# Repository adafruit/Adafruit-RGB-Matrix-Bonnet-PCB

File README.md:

## Adafruit RGB LED Matrix Display Bonnet PCB

<a href="http://www.adafruit.com/products/3211"><br/>
Click here to purchase one from the Adafruit shop</a>

PCB files for the Adafruit RGB Matrix Bonnet. Format is EagleCAD schematic and board layout

For more details, check out the product page at
* https://www.adafruit.com/product/3211

### Description

You can now create a dazzling display with your Raspberry Pi with the Adafruit RGB Matrix Bonnet. These boards plug into your Pi and makes it super easy to control RGB matrices such as those we stock in the shop and create a colorful scrolling display or mini LED wall with ease.

"Bonnet" boards work on any Raspberry Pi with a 40-pin GPIO header — Zero, Zero W/WH, Model A+, B+, Pi 2 and Pi 3. They do not work with older 26-pin boards like the original Model A or B. Note with the Pi Zero you may need to solder a header on the Pi board; it’s normally unpopulated on that model.

We also have an older, HAT version of our RGB Matrix design. The HAT version does not come fully assembled, does not support 1/32-scan matrices, but does come with a real time clock (RTC)

This bonnet will make your matrix projects super easy and avoids wiring complexity.

Please note: this Bonnet is only for use with HUB75 type RGB matrices. Not for use with NeoPixel, DotStar, or other 'addressable' LEDs.

### License

Adafruit invests time and resources providing this open source design, please support Adafruit and open-source hardware by purchasing products from [Adafruit](https://www.adafruit.com)!

Designed for Adafruit Industries.

Creative Commons Attribution/Share-Alike, all text above must be included in any redistribution. See license.txt for additional details.

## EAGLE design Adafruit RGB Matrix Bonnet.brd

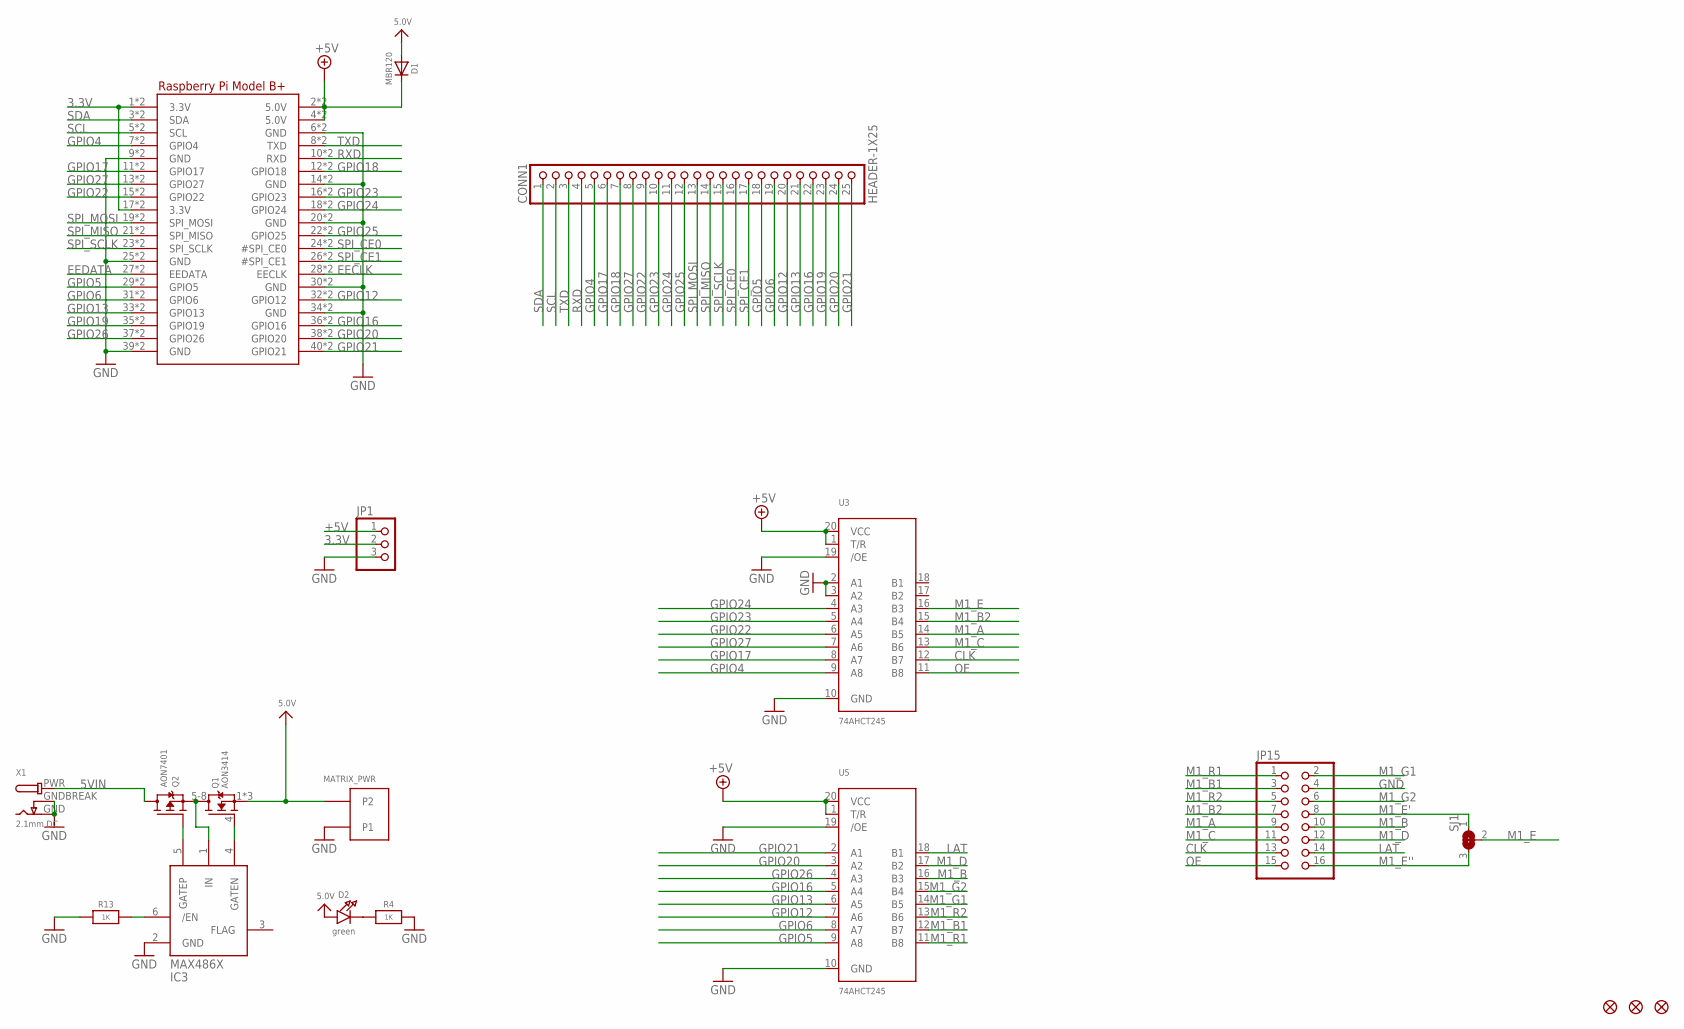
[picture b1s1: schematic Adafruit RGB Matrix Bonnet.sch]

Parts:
CONN1: HEADER-1X25; 1X25_ROUND_70MIL
D1: MBR120; SOD-123
D2: green; CHIPLED_0805_NOOUTLINE
FID1, FID2, FID3: FIDUCIAL_1MM
IC3: MAX4866T; SOT23-6
JP1: HEADER-1X376MIL; 1X03_ROUND_76
JP15: HEADER-2X8_SHROUDED; 2X08_SHROUDED
MATRIX_PWR: PINHEAD; TERMBLOCK508
Q1: AON3414; POWERPAK-1212-8
Q2: AON7401; POWERDI3333
R4, R13: 1K; 0805-NO
RPI1: RASPBERRYPI_BPLUS_BONNET_THMSMT; PI_BONNET_THMSMT
SJ1: SOLDERJUMPER_2WAY; SOLDERJUMPER_2WAY_OPEN_NOPASTE
U3, U5: 74AHCT245; TSSOP20
X1: 2.1mm DC; DCJACK_2MM_PTH

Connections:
3.3V: JP1.2, RPI1.1 (3.3V), RPI1.17 (3.3V), RPI1.S1 (3.3V), RPI1.S17 (3.3V)
5.0V: D1.A, D2.A, MATRIX_PWR.P$4 (P2), Q1.1 (S), Q1.2 (S), Q1.3 (S)
5VIN: Q2.5678 (D), X1.PWR
+5V: D1.C, JP1.1, RPI1.2 (5.0V), RPI1.4 (5.0V), RPI1.S2 (5.0V), RPI1.S4 (5.0V), U3.1 (T/R), U3.20 (VCC), U5.1 (T/R), U5.20 (VCC)
CLK: JP15.13, U3.12 (B7)
EECLK: RPI1.28 (EECLK), RPI1.S28 (EECLK)
EEDATA: RPI1.27 (EEDATA), RPI1.S27 (EEDATA)
GND: IC3.2 (GND), JP1.3, JP15.4, MATRIX_PWR.P$3 (P1), R4.2, R13.1, RPI1.6 (GND), RPI1.9 (GND), RPI1.14 (GND), RPI1.20 (GND), RPI1.25 (GND), RPI1.30 (GND), RPI1.34 (GND), RPI1.39 (GND), RPI1.S6 (GND), RPI1.S9 (GND), RPI1.S14 (GND), RPI1.S20 (GND), RPI1.S25 (GND), RPI1.S30 (GND), RPI1.S34 (GND), RPI1.S39 (GND), U3.2 (A1), U3.3 (A2), U3.10 (GND), U3.19 (/OE), U5.10 (GND), U5.19 (/OE), X1.GND, X1.GNDBREAK
GPIO4: CONN1.5, RPI1.7 (GPIO4), RPI1.S7 (GPIO4), U3.9 (A8)
GPIO5: CONN1.18, RPI1.29 (GPIO5), RPI1.S29 (GPIO5), U5.9 (A8)
GPIO6: CONN1.19, RPI1.31 (GPIO6), RPI1.S31 (GPIO6), U5.8 (A7)
GPIO12: CONN1.20, RPI1.32 (GPIO12), RPI1.S32 (GPIO12), U5.7 (A6)
GPIO13: CONN1.21, RPI1.33 (GPIO13), RPI1.S33 (GPIO13), U5.6 (A5)
GPIO16: CONN1.22, RPI1.36 (GPIO16), RPI1.S36 (GPIO16), U5.5 (A4)
GPIO17: CONN1.6, RPI1.11 (GPIO17), RPI1.S11 (GPIO17), U3.8 (A7)
GPIO18: CONN1.7, RPI1.12 (GPIO18), RPI1.S12 (GPIO18)
GPIO19: CONN1.23, RPI1.35 (GPIO19), RPI1.S35 (GPIO19)
GPIO20: CONN1.24, RPI1.38 (GPIO20), RPI1.S38 (GPIO20), U5.3 (A2)
GPIO21: CONN1.25, RPI1.40 (GPIO21), RPI1.S40 (GPIO21), U5.2 (A1)
GPIO22: CONN1.9, RPI1.15 (GPIO22), RPI1.S15 (GPIO22), U3.6 (A5)
GPIO23: CONN1.10, RPI1.16 (GPIO23), RPI1.S16 (GPIO23), U3.5 (A4)
GPIO24: CONN1.11, RPI1.18 (GPIO24), RPI1.S18 (GPIO24), U3.4 (A3)
GPIO25: CONN1.12, RPI1.22 (GPIO25), RPI1.S22 (GPIO25)
GPIO26: RPI1.37 (GPIO26), RPI1.S37 (GPIO26), U5.4 (A3)
GPIO27: CONN1.8, RPI1.13 (GPIO27), RPI1.S13 (GPIO27), U3.7 (A6)
LAT: JP15.14, U5.18 (B1)
M1_A: JP15.9, U3.14 (B5)
M1_B: JP15.10, U5.16 (B3)
M1_B1: JP15.3, U5.12 (B7)
M1_B2: JP15.7, U3.15 (B4)
M1_C: JP15.11, U3.13 (B6)
M1_D: JP15.12, U5.17 (B2)
M1_E: SJ1.2, U3.16 (B3)
M1_E': JP15.8, SJ1.1
M1_E'': JP15.16, SJ1.3
M1_G1: JP15.2, U5.14 (B5)
M1_G2: JP15.6, U5.15 (B4)
M1_R1: JP15.1, U5.11 (B8)
M1_R2: JP15.5, U5.13 (B6)
unnamed: IC3.6 (/EN), R13.2
unnamed: D2.C, R4.1
unnamed: IC3.1 (IN), Q1.5-8 (D), Q2.1 (S), Q2.2 (S), Q2.3 (S)
unnamed: IC3.4 (GATEN), Q1.4 (G)
unnamed: IC3.5 (GATEP), Q2.4 (G)
OE: JP15.15, U3.11 (B8)
RXD: CONN1.4, RPI1.10 (RXD), RPI1.S10 (RXD)
SCL: CONN1.2, RPI1.5 (SCL), RPI1.S5 (SCL)
SDA: CONN1.1, RPI1.3 (SDA), RPI1.S3 (SDA)
SPI_CE0: CONN1.16, RPI1.24 (#SPI_CE0), RPI1.S24 (#SPI_CE0)
SPI_CE1: CONN1.17, RPI1.26 (#SPI_CE1), RPI1.S26 (#SPI_CE1)
SPI_MISO: CONN1.14, RPI1.21 (SPI_MISO), RPI1.S21 (SPI_MISO)
SPI_MOSI: CONN1.13, RPI1.19 (SPI_MOSI), RPI1.S19 (SPI_MOSI)
SPI_SCLK: CONN1.15, RPI1.23 (SPI_SCLK), RPI1.S23 (SPI_SCLK)
TXD: CONN1.3, RPI1.8 (TXD), RPI1.S8 (TXD)

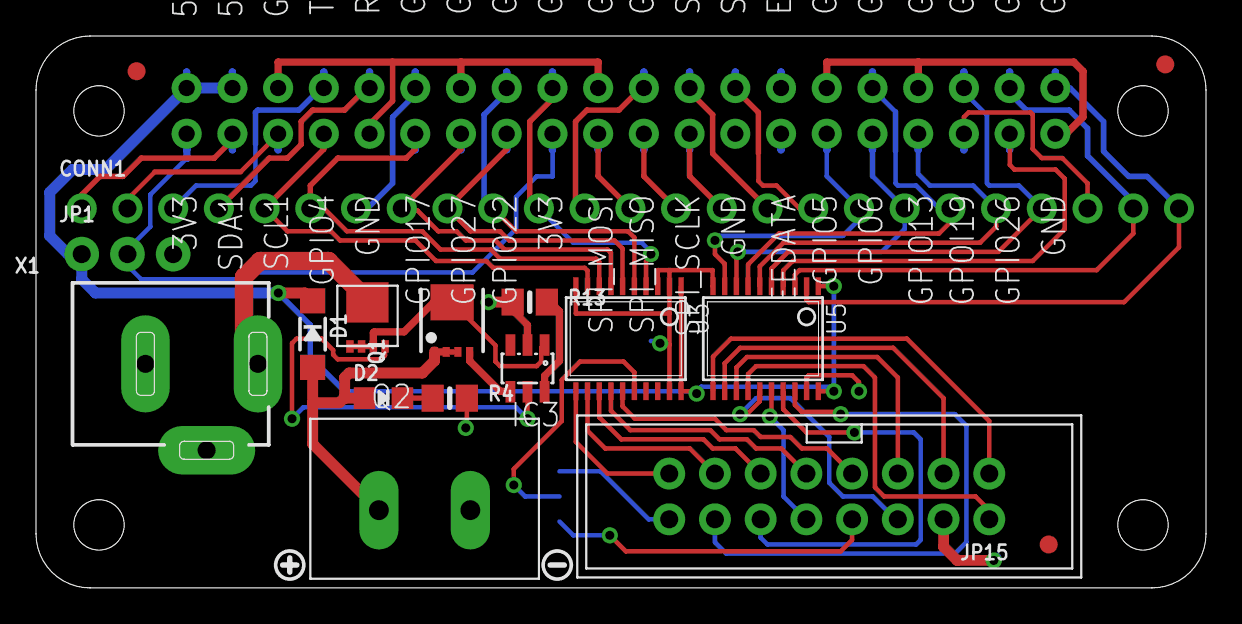
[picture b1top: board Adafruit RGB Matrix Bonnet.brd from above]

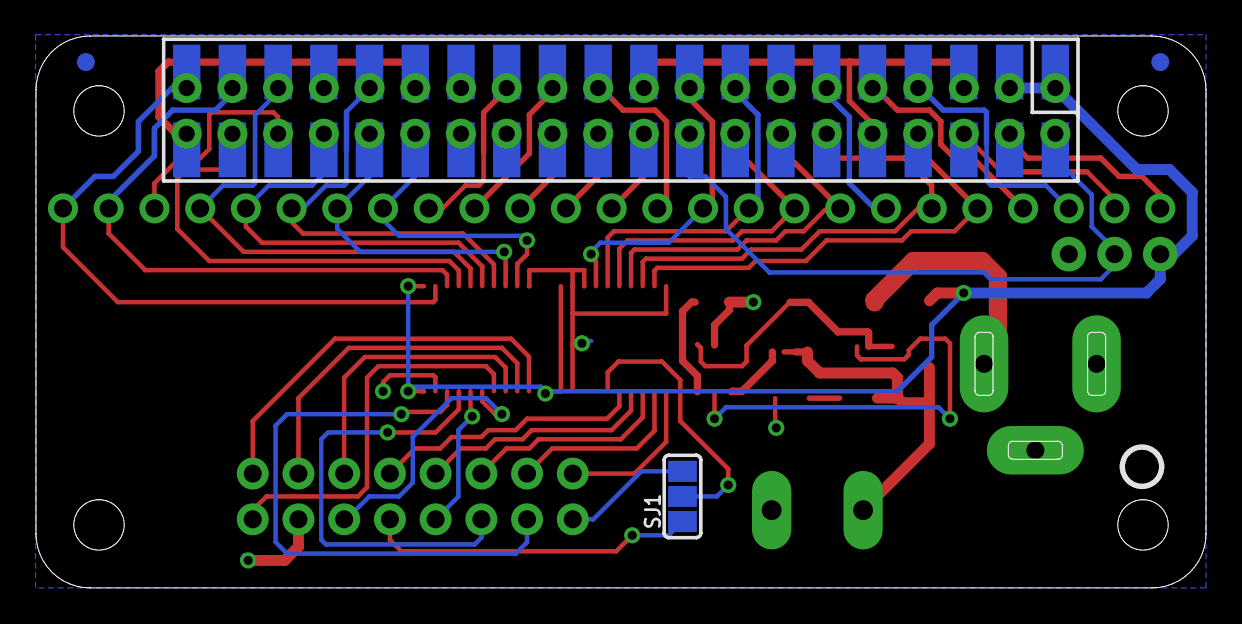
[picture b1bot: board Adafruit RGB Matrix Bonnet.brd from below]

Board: 2 copper layers, 65.0 x 30.7 mm, 24 parts (3 on the bottom side), 54 nets.

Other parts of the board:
U$1: BONNET_MATRIX_TOP
U$3: PCBFEAT-REV-056
U$6: BONNET_MATRIX_BOT
U$10: SYMBOL_PLUS
U$11: SYMBOL_MINUS

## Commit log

2018-02-14 glowwwy

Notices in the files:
parts and their libraries:
microbuilder: This work is placed in the public domain, and may be freely used for commercial and non-commercial work with the following conditions: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
